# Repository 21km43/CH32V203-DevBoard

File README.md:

# CH32V203 Development Board

## Summary
Schematic and Board layout of CH32V203 Development Board. This project was created using [KiCAD 8](https://www.kicad.org/).

## MCU
[CH32V203C8T6](https://www.wch-ic.com/products/CH32V203.html)  
144MHz, 20KB RAM, 64KB ROM  

## Features
* CH32V203C8T6 RISC-V
* `144 MHz` maximum frequency, `64 KB` of Flash memory, `20 KB` of SRAM
* `8 MHz` crystal (High-Speed Enternal Clock)
* `32.768 KHz` crystal (Low-Speed External Clock)
* Frequency deviation of crystal has been tested (on FR-4 board with a thickness of 1.6 mm)
* White LED for `PC13`
* 2x20 side pins
* Size: `50.80 mm x 20.32 mm`
* USB Device (Type-C)
  * PA11 USB1_DM
  * PA12 USB1_DP
* USB Host (Type-C)
  * PB6 USB2_DM
  * PB7 USB2_DP
* All component parameters are already set for [JLCPCB](https://jlcpcb.com). (Thanks for [Fabrication Toolkit](https://github.com/bennymeg/Fabrication-Toolkit))
  * Tooling Hole for SMT Assembly has been added.

## Solder jumpers
* JP1 ... If this jumper is opened, 3.3V cannot be output from the USB or 5V pins through the LDO regulator, and power must be supplied to the MCU from 3.3V. Instead, the quiescent current of the LDO regulator can be set to 0, which optimizes power consumption.
* JP2 ... Shorting this jumper disables the back-flow protection from the 5V pin to the USB input; short it when you want to output 5V from the USB to 5V with no voltage drop or when you want to use the 5V pin to power the USB2 output. Do not supply power from both the 5V pin and USB while shorted. Note that shorting this pin will increase current consumption by about 0.1~0.2mA due to the pull-down resistor on the CC pin.
* JP3 ... Shorting all of these jumpers changes the function of USB2 from Host to Device and allows it to receive power from USB2. In this case, it is not recommended to use USB1 and USB2 at the same time (because of the risk of short circuits if the voltages of USB1 and USB2 are different)

## Parts List
You can see parts list from the BOM below.  
[Parts List](/production/bom.csv)

## Schematic and Board image
[Board schematic](CH32V203-DevBoard.pdf)  

## LICENSE
[MIT LICENSE](/LICENSE)  
You may use it freely for personal use, but if you wish to use it for commercial purposes, I would appreciate it if you could contact me.

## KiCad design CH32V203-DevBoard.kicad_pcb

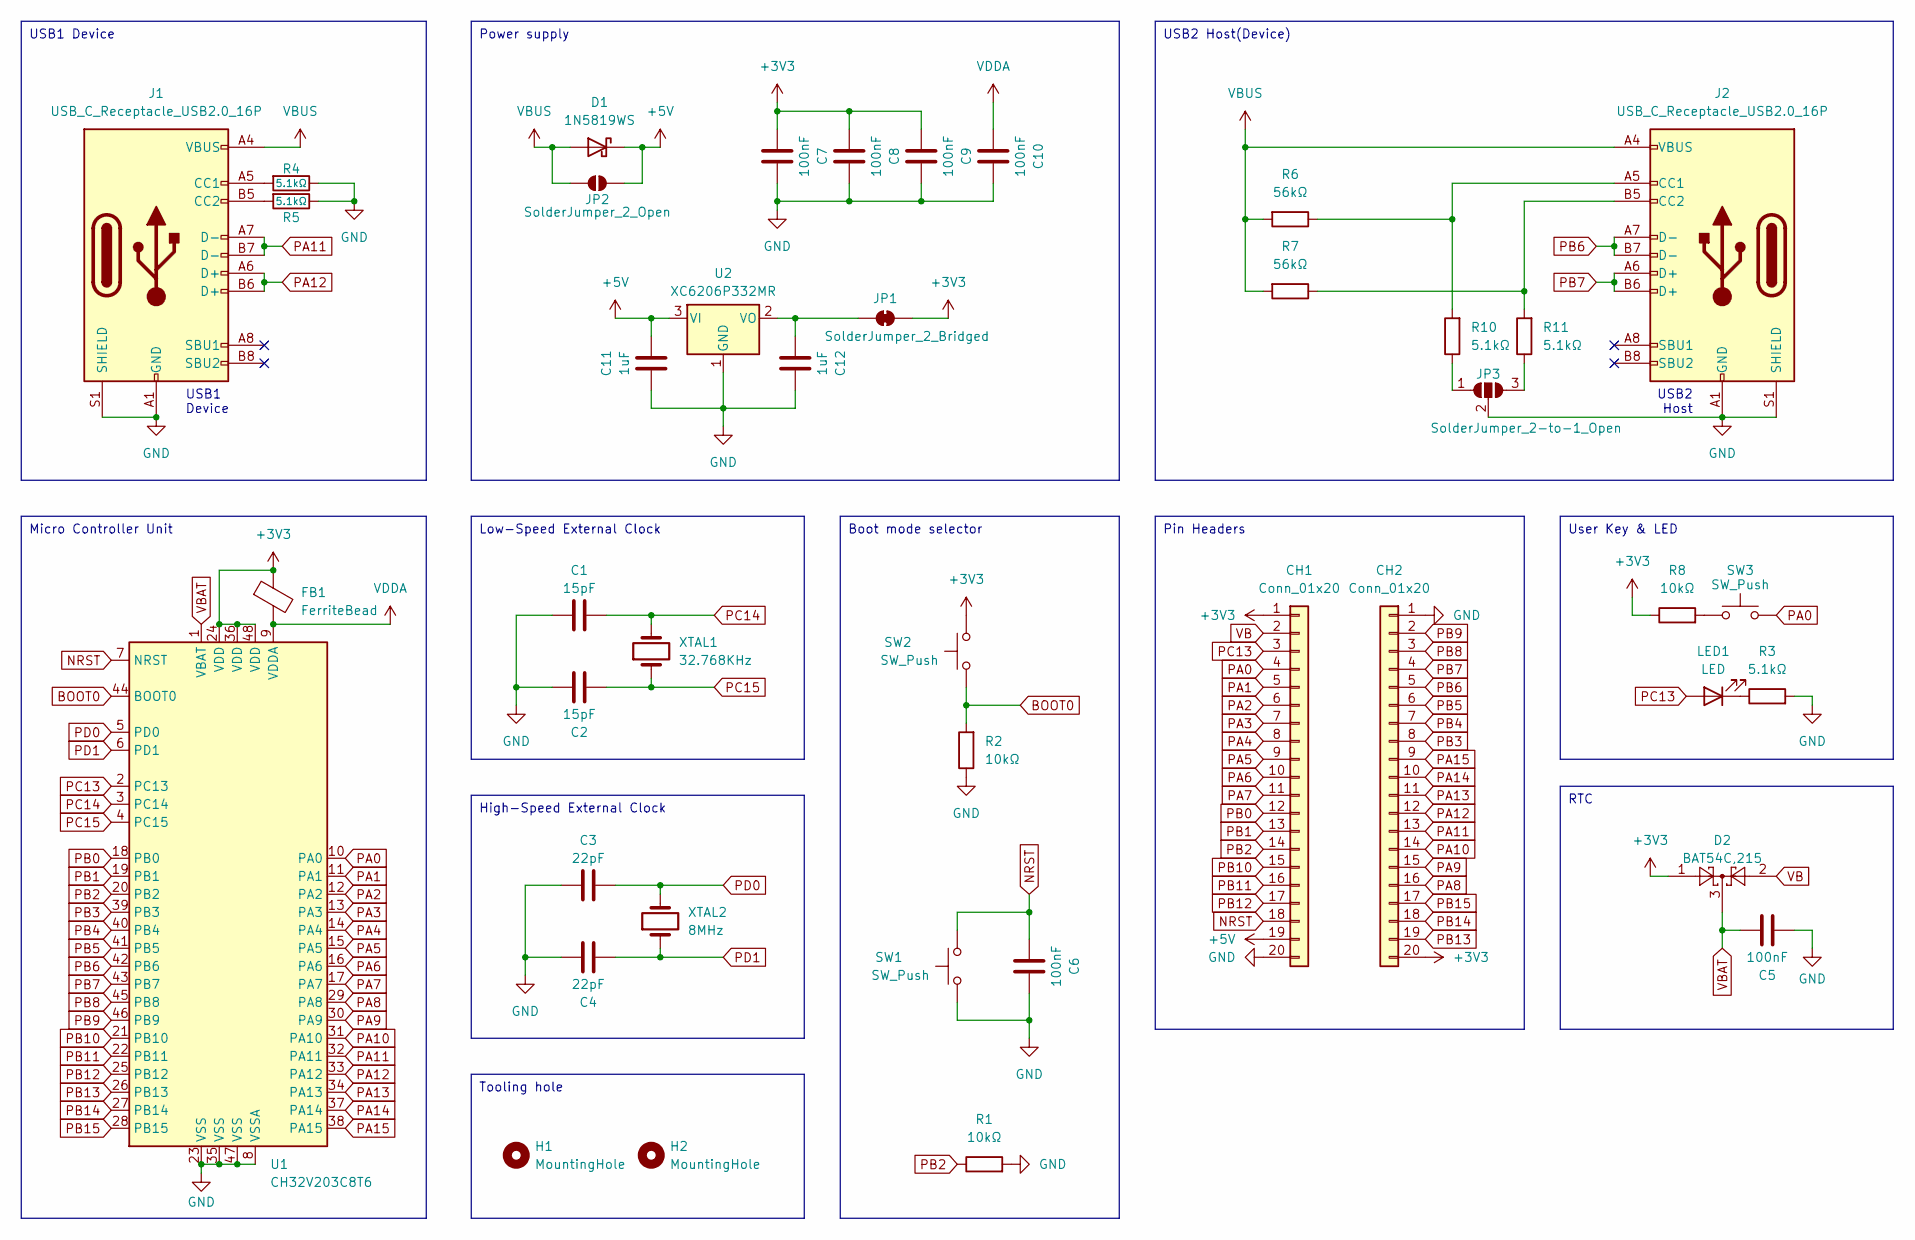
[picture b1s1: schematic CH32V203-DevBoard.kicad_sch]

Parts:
C1, C2: 15pF; C_0402_1005Metric; LCSC C1548
C3, C4: 22pF; C_0402_1005Metric; LCSC C1555
C5, C6, C7, C8, C9, C10: 100nF; C_0402_1005Metric; LCSC C1525
C11, C12: 1uF; C_0603_1608Metric; LCSC C15849
CH1, CH2: Conn_01x20; PinHeader_1x20_P2.54mm_Vertical
D1: 1N5819WS; D_SOD-323; LCSC C191023
D2: BAT54C,215; SOT-23; LCSC C37704
FB1: FerriteBead; L_0603_1608Metric; LCSC C1002
H1, H2: MountingHole; Tooling_Hole
J1, J2: USB_C_Receptacle_USB2.0_16P; USB_C_Receptacle_XKB_U262-16XN-4BVC11; LCSC C2988369
JP1: SolderJumper_2_Bridged; SolderJumper-2_P1.3mm_Bridged_RoundedPad1.0x1.5mm
JP2: SolderJumper_2_Open; SolderJumper-2_P1.3mm_Open_RoundedPad1.0x1.5mm
JP3: SolderJumper_2-to-1_Open; SolderJumper-2-to-1_P0.9mm_Open
LED1: LED; LED_0603_1608Metric; LCSC C2290
R1, R2, R8: 10kΩ; R_0402_1005Metric; LCSC C25744
R3, R4, R5, R10, R11: 5.1kΩ; R_0402_1005Metric; LCSC C25905
R6, R7: 56kΩ; R_0603_1608Metric; LCSC C23206
SW1, SW2, SW3: SW_Push; SW_SPST_PTS810; LCSC C115360
U1: CH32V203C8T6; LQFP-48_7x7mm_P0.5mm; LCSC C3001172
U2: XC6206P332MR; SOT-23-3; LCSC C5446
XTAL1: 32.768KHz; Crystal_SMD_3215-2Pin_3.2x1.5mm; LCSC C32346
XTAL2: 8MHz; Crystal_SMD_5032-2Pin_5.0x3.2mm; LCSC C115962

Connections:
+3V3: C7.1, C8.1, C9.1, CH1.1, CH2.20, D2.1, FB1.1, JP1.2 (B), R8.1, SW2.2, U1.24 (VDD), U1.36 (VDD), U1.48 (VDD)
+5V: C11.1, CH1.19, D1.1 (K), JP2.2 (B), U2.3 (VI)
BOOT0: R2.2, SW2.1, U1.44 (BOOT0)
GND: C1.1, C2.2, C3.1, C4.2, C5.1, C6.2, C7.2, C8.2, C9.2, C10.2, C11.2, C12.2, CH1.20, CH2.1, J1.A1 (GND), J1.A12 (GND), J1.B1 (GND), J1.B12 (GND), J1.S1 (SHIELD), J2.A1 (GND), J2.A12 (GND), J2.B1 (GND), J2.B12 (GND), J2.S1 (SHIELD), JP3.2 (C), R1.2, R2.1, R3.2, R4.1, R5.1, SW1.1, U1.8 (VSSA), U1.23 (VSS), U1.35 (VSS), U1.47 (VSS), U2.1 (GND)
NRST: C6.1, CH1.18, SW1.2, U1.7 (NRST)
unnamed: J1.A5 (CC1), R4.2
unnamed: J1.B5 (CC2), R5.2
unnamed: J2.A5 (CC1), R6.1, R10.2
unnamed: J2.B5 (CC2), R7.1, R11.2
unnamed: C12.1, JP1.1 (A), U2.2 (VO)
unnamed: JP3.1 (A), R10.1
unnamed: JP3.3 (B), R11.1
unnamed: LED1.1 (K), R3.1
unnamed: R8.2, SW3.1
PA0: CH1.4, SW3.2, U1.10 (PA0)
PA1: CH1.5, U1.11 (PA1)
PA2: CH1.6, U1.12 (PA2)
PA3: CH1.7, U1.13 (PA3)
PA4: CH1.8, U1.14 (PA4)
PA5: CH1.9, U1.15 (PA5)
PA6: CH1.10, U1.16 (PA6)
PA7: CH1.11, U1.17 (PA7)
PA8: CH2.16, U1.29 (PA8)
PA9: CH2.15, U1.30 (PA9)
PA10: CH2.14, U1.31 (PA10)
PA11: CH2.13, J1.A7 (D-), J1.B7 (D-), U1.32 (PA11)
PA12: CH2.12, J1.A6 (D+), J1.B6 (D+), U1.33 (PA12)
PA13: CH2.11, U1.34 (PA13)
PA14: CH2.10, U1.37 (PA14)
PA15: CH2.9, U1.38 (PA15)
PB0: CH1.12, U1.18 (PB0)
PB1: CH1.13, U1.19 (PB1)
PB2: CH1.14, R1.1, U1.20 (PB2)
PB3: CH2.8, U1.39 (PB3)
PB4: CH2.7, U1.40 (PB4)
PB5: CH2.6, U1.41 (PB5)
PB6: CH2.5, J2.A7 (D-), J2.B7 (D-), U1.42 (PB6)
PB7: CH2.4, J2.A6 (D+), J2.B6 (D+), U1.43 (PB7)
PB8: CH2.3, U1.45 (PB8)
PB9: CH2.2, U1.46 (PB9)
PB10: CH1.15, U1.21 (PB10)
PB11: CH1.16, U1.22 (PB11)
PB12: CH1.17, U1.25 (PB12)
PB13: CH2.19, U1.26 (PB13)
PB14: CH2.18, U1.27 (PB14)
PB15: CH2.17, U1.28 (PB15)
PC13: CH1.3, LED1.2 (A), U1.2 (PC13)
PC14: C1.2, U1.3 (PC14), XTAL1.2
PC15: C2.1, U1.4 (PC15), XTAL1.1
PD0: C3.2, U1.5 (PD0), XTAL2.2
PD1: C4.1, U1.6 (PD1), XTAL2.1
VB: CH1.2, D2.2
VBAT: C5.2, D2.3, U1.1 (VBAT)
VBUS: D1.2 (A), J1.A4 (VBUS), J1.A9 (VBUS), J1.B4 (VBUS), J1.B9 (VBUS), J2.A4 (VBUS), J2.A9 (VBUS), J2.B4 (VBUS), J2.B9 (VBUS), JP2.1 (A), R6.2, R7.2
VDDA: C10.1, FB1.2, U1.9 (VDDA)

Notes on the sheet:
USB1 Device
Pin Headers
Tooling hole
USB2 Host(Device)
RTC
High-Speed External Clock
Micro Controller Unit
Boot mode selector
User Key & LED
Power supply
Low-Speed External Clock
USB2 Host
USB1 Device

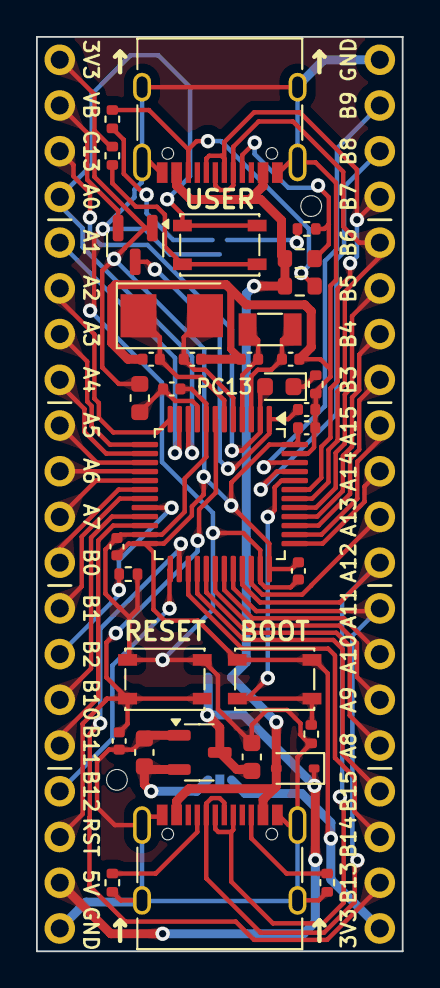
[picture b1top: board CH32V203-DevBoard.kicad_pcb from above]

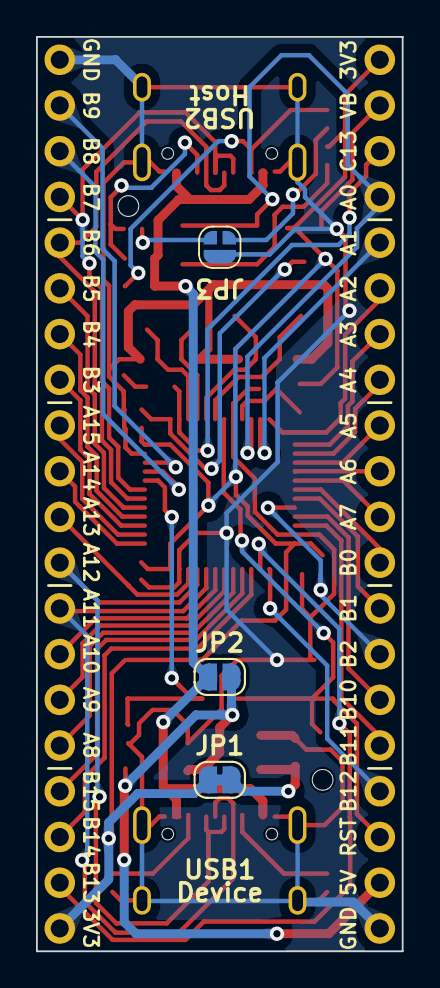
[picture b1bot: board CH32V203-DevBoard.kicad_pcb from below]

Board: 2 copper layers, 20.3 x 50.8 mm, 42 parts (5 on the bottom side), 55 nets.

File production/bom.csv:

Designator,Footprint,Quantity,Value,LCSC Part #
"C1, C2",0402,2,15pF,C1548
"C10, C5, C6, C7, C8, C9",0402,6,100nF,C1525
"C11, C12",0603,2,1uF,C15849
"C3, C4",0402,2,22pF,C1555
D1,D_SOD-323,1,1N5819WS,C191023
D2,SOT-23,1,"BAT54C,215",C37704
FB1,0603,1,FerriteBead,C1002
"J1, J2",USB_C_Receptacle_XKB_U262-16XN-4BVC11,2,USB_C_Receptacle_USB2.0_16P,C2988369
LED1,0603,1,LED,C2290
"R1, R2, R8",0402,3,10kΩ,C25744
"R10, R11, R3, R4, R5",0402,5,5.1kΩ,C25905
"R6, R7",0603,2,56kΩ,C23206
"SW1, SW2, SW3",SW_SPST_PTS810,3,SW_Push,C115360
U1,LQFP-48_7x7mm_P0.5mm,1,CH32V203C8T6,C3001172
U2,SOT-23-3,1,XC6206P332MR,C5446
XTAL1,Crystal_SMD_3215-2Pin_3.2x1.5mm,1,32.768KHz,C32346
XTAL2,Crystal_SMD_5032-2Pin_5.0x3.2mm,1,8MHz,C115962

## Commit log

2024-05-24 reference renaming
2024-05-24 Update LICENSE
2024-05-24 change solid pattern
2024-05-24 gnd pattern fix
2024-05-27 user key resistor fix
2024-05-27 silk fix
2024-05-27 cc resistor fix
2024-05-30 add host vbus switch
2024-05-31 board fix
2024-06-01 crystal load capacitor fix
2024-06-02 fix rotation offset and readme
2024-06-02 配線・シルクを微調整
2024-06-03 USB周りの配線や裏面シルクの修正
2024-06-03 画像・gitignore更新
2024-06-06 add usb2 device solder jumper
2024-06-06 fix JLCPCB Offset
2024-06-06 pulldown resistor fix
2024-06-06 remove unused property
2024-06-07 fix wire width
2024-06-07 show reference number
2024-06-07 jp3 fix
2024-06-07 jumper footprint fix
2024-06-08 fix default usb position
2024-06-08 change usb component
2024-06-28 change image
2024-07-11 change ldo and add PA0 switch
2024-09-17 USBFS resistor fix
